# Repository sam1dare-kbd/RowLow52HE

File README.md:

# RowLow52HE

RowLow52HE is a 50% Hall-effect keyboard based on the [HE60](https://github.com/peppapighs/HE60) project. <br>

RowLow52HEは、HE60プロジェクトをベースにして設計した50%の磁気キーボードです。<br>
<br>

---

# Build Guide  

https://note.com/sam1dare/n/naa1372ecf801 <br>
(Japanese text only.)

---

# Important Notes 

This keyboard uses magnetic sensors and may become warm around the MCU during operation. <br>
If you notice abnormal heat generation or unexpected behavior, stop using the device and inspect it before further use.<br><br>

本キーボードは磁気センサーを使用しているため、使用環境によってはMCU周辺が温かくなる場合があります。<br>
異常な発熱や動作不良が発生した場合は、使用を中止してください。

---

# HE60 (Original Project)

Below is the original README from the HE60 project, which this keyboard is based on.

---

# HE60

HE60 is a 60% Hall-effect keyboard PCB with 8kHz polling rate, a split spacebar and Tsangan layout support.

## Features

- Support for GH60 tray mount cases e.g., KBDfans Tofu60 Redux, and KBDfans Holy60.
- Support for gummy O-ring mount cases **if the USB-C port is not soldered** e.g., Bakeneko60, and SingaKBD Unikorn (required 10mm JST cable).
- [libhmk](https://github.com/peppapighs/libhmk) firmware.
- [hmkconf](https://hmk.prasertsuk.com) web-based configurator.

## Disclaimer

- The PCB requires standoffs to be mounted to the switch plate. The mounting points are **not compatible** with other available plates e.g., GEON Venom60 7U plate. HE60 v1 plate **is not compatible** with this PCB.

## Supported Layouts

## Fabrication

The following files are required:

- BOM (Bill of Materials): Contains the list of components required to build the PCB.
- Pick and Place: Contains the placement of the components on the PCB.
- Gerber: Contains the PCB design files for fabrication.

Note that the components in the BOM are all mounted on the bottom side of the PCB, and are based on the available components in JLCPCB at the time of writing. You may need to adjust the components based on your preference or availability. For the JST connector (labeled `JST_SH`), I used `WAFER-SH1.0-4PWB` offered by JLCPCB. **Make sure to deselect the USB-C port when choosing the components to solder if you are using the gummy O-ring version.**

You may change the Hall-effect sensors during the component selection based on your preference, and availability. Different sensors require different calibration values, which can be adjusted using the web-based configurator. Here are some options that I have used:

- GH39FKSW (Cheapest)
- MT9102ET
- SS39ET
- DRV5055A3
- OH49E-S (Discontinued)

The fabrication files above are available [here](https://github.com/peppapighs/HE60/releases).

## Build Guide

The following items are required to build the PCB:

- PCB
- Switch plate (DXF file available [here](/plate.dxf). You may need to use less flexible materials such as aluminum or FR4 to prevent the switch at the top right corner from popping out if you use the alternative backspace layout. If you would like to manufacture FR4 plate along with the PCB, you can find the GERBER file for the plate [here](https://github.com/peppapighs/HE60/releases).)
- Magnetic switches (e.g., GEON Raw HE, Gateron Magnetic Jade, Duhuk Core HE, etc.)
- Stabilizers (**Clip-in stabilizers are required for the gummy O-ring version**)
- M2 3.5mm standoffs x8
- M2 3mm flat head screws x16

1. Install the stabilizers to the PCB.

2. Attach the standoffs to the PCB using the M2 screws.

3. Install the switches to the plate. Assemble the plate and PCB together. Press the PCB against the plate to make sure the switches are seated properly. Screw the standoffs to the plate using the rest of the M2 screws.

4. Install the PCB into the case.

## Firmware

Head to [libhmk](https://github.com/peppapighs/libhmk/releases) for a pre-compiled firmware. The firmware can be flashed using DFU mode, which can be entered by holding the BOOT button before plugging in. You may need to install the DFU bootloader driver using Zadig. See [libhmk](https://github.com/peppapighs/libhmk) for more information for firmware flashing instructions.

## Acknowledgements

- Xelus from AEBoards for reviewing the PCB design and providing feedback.
- Keyboard Atelier community for supporting the project.

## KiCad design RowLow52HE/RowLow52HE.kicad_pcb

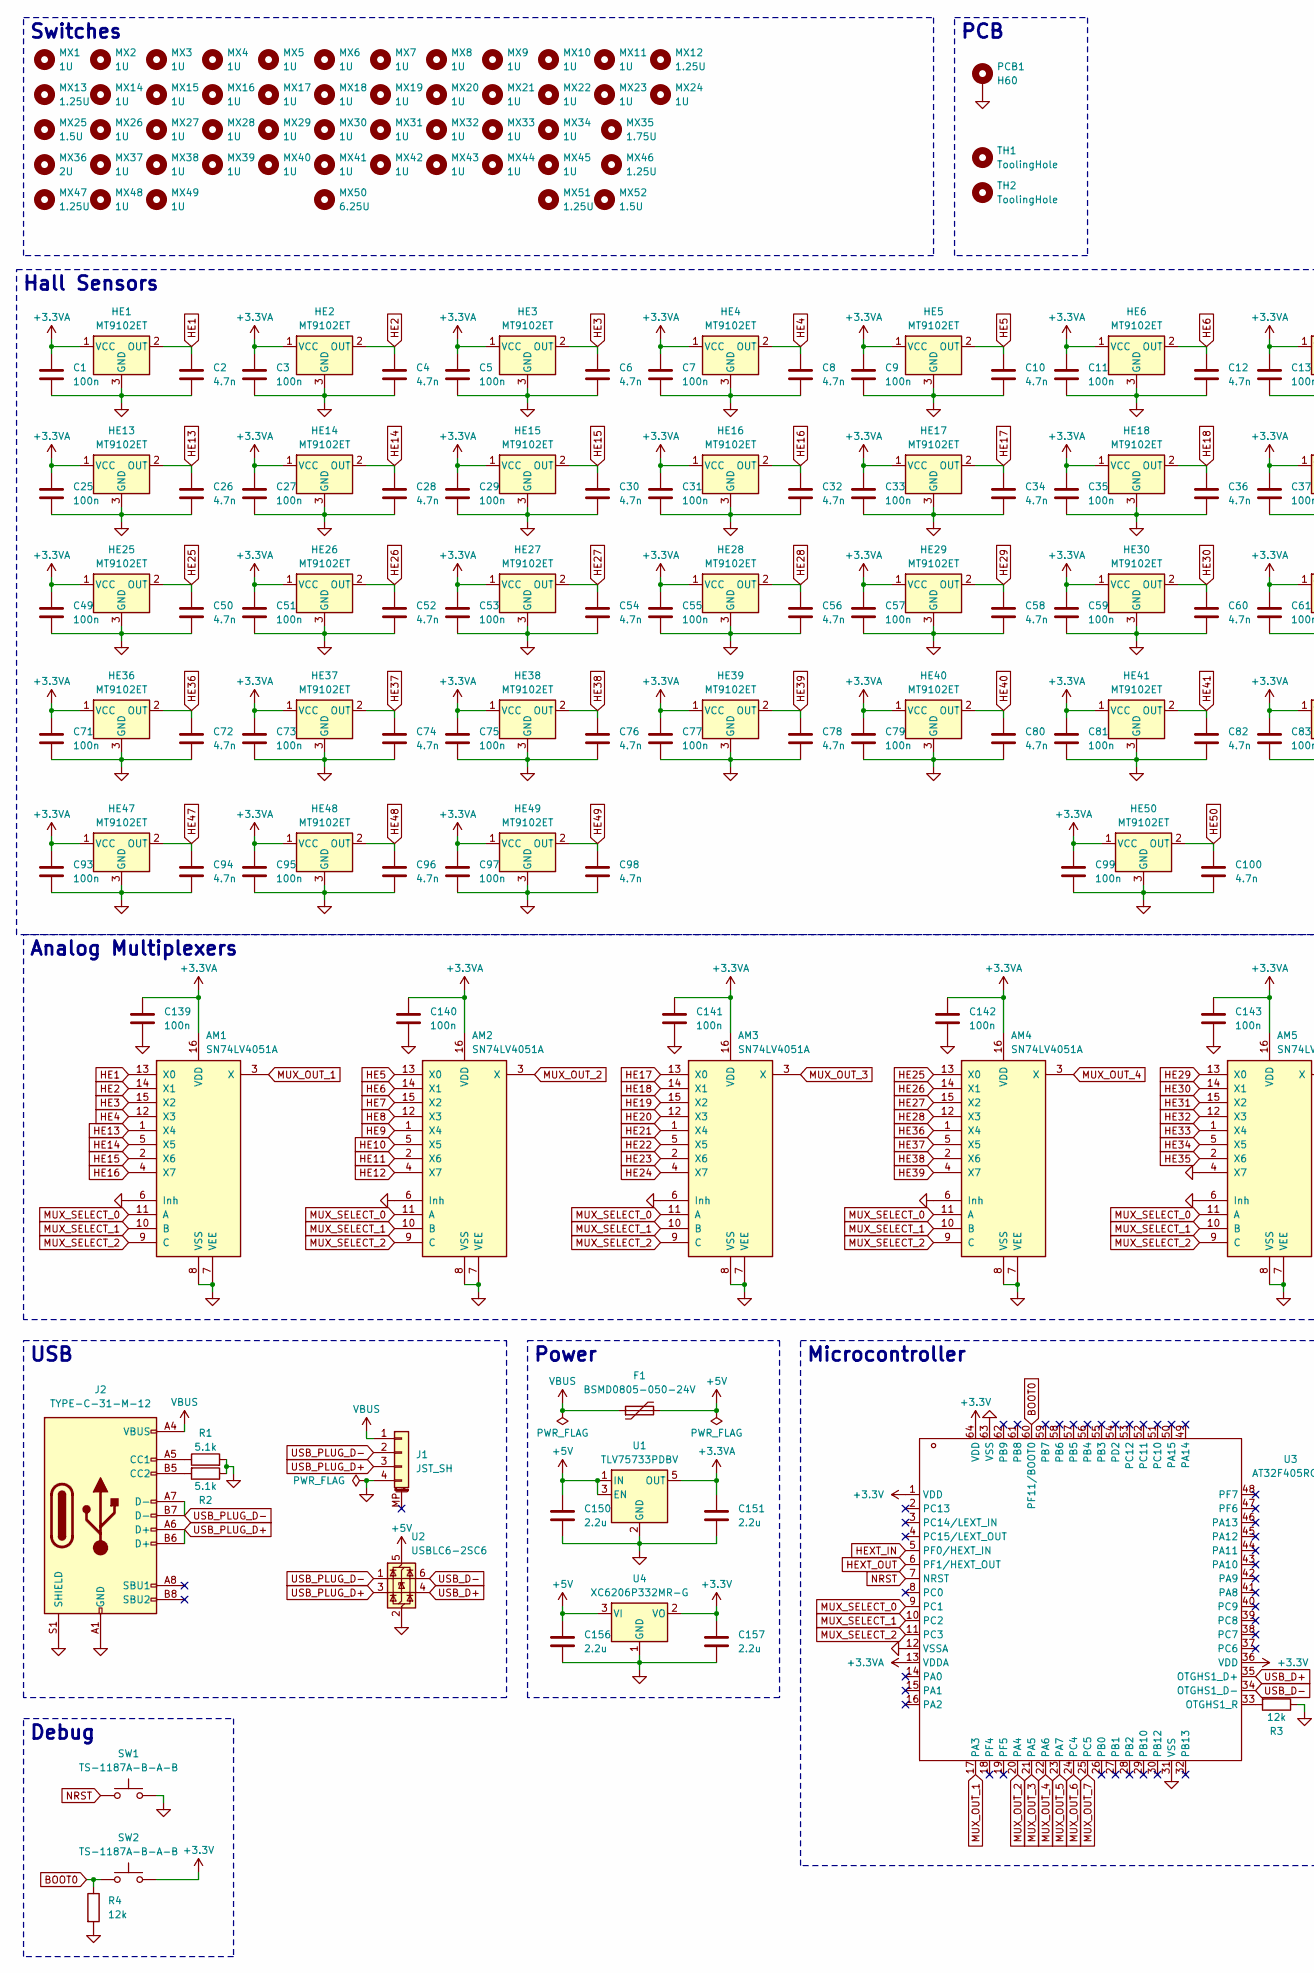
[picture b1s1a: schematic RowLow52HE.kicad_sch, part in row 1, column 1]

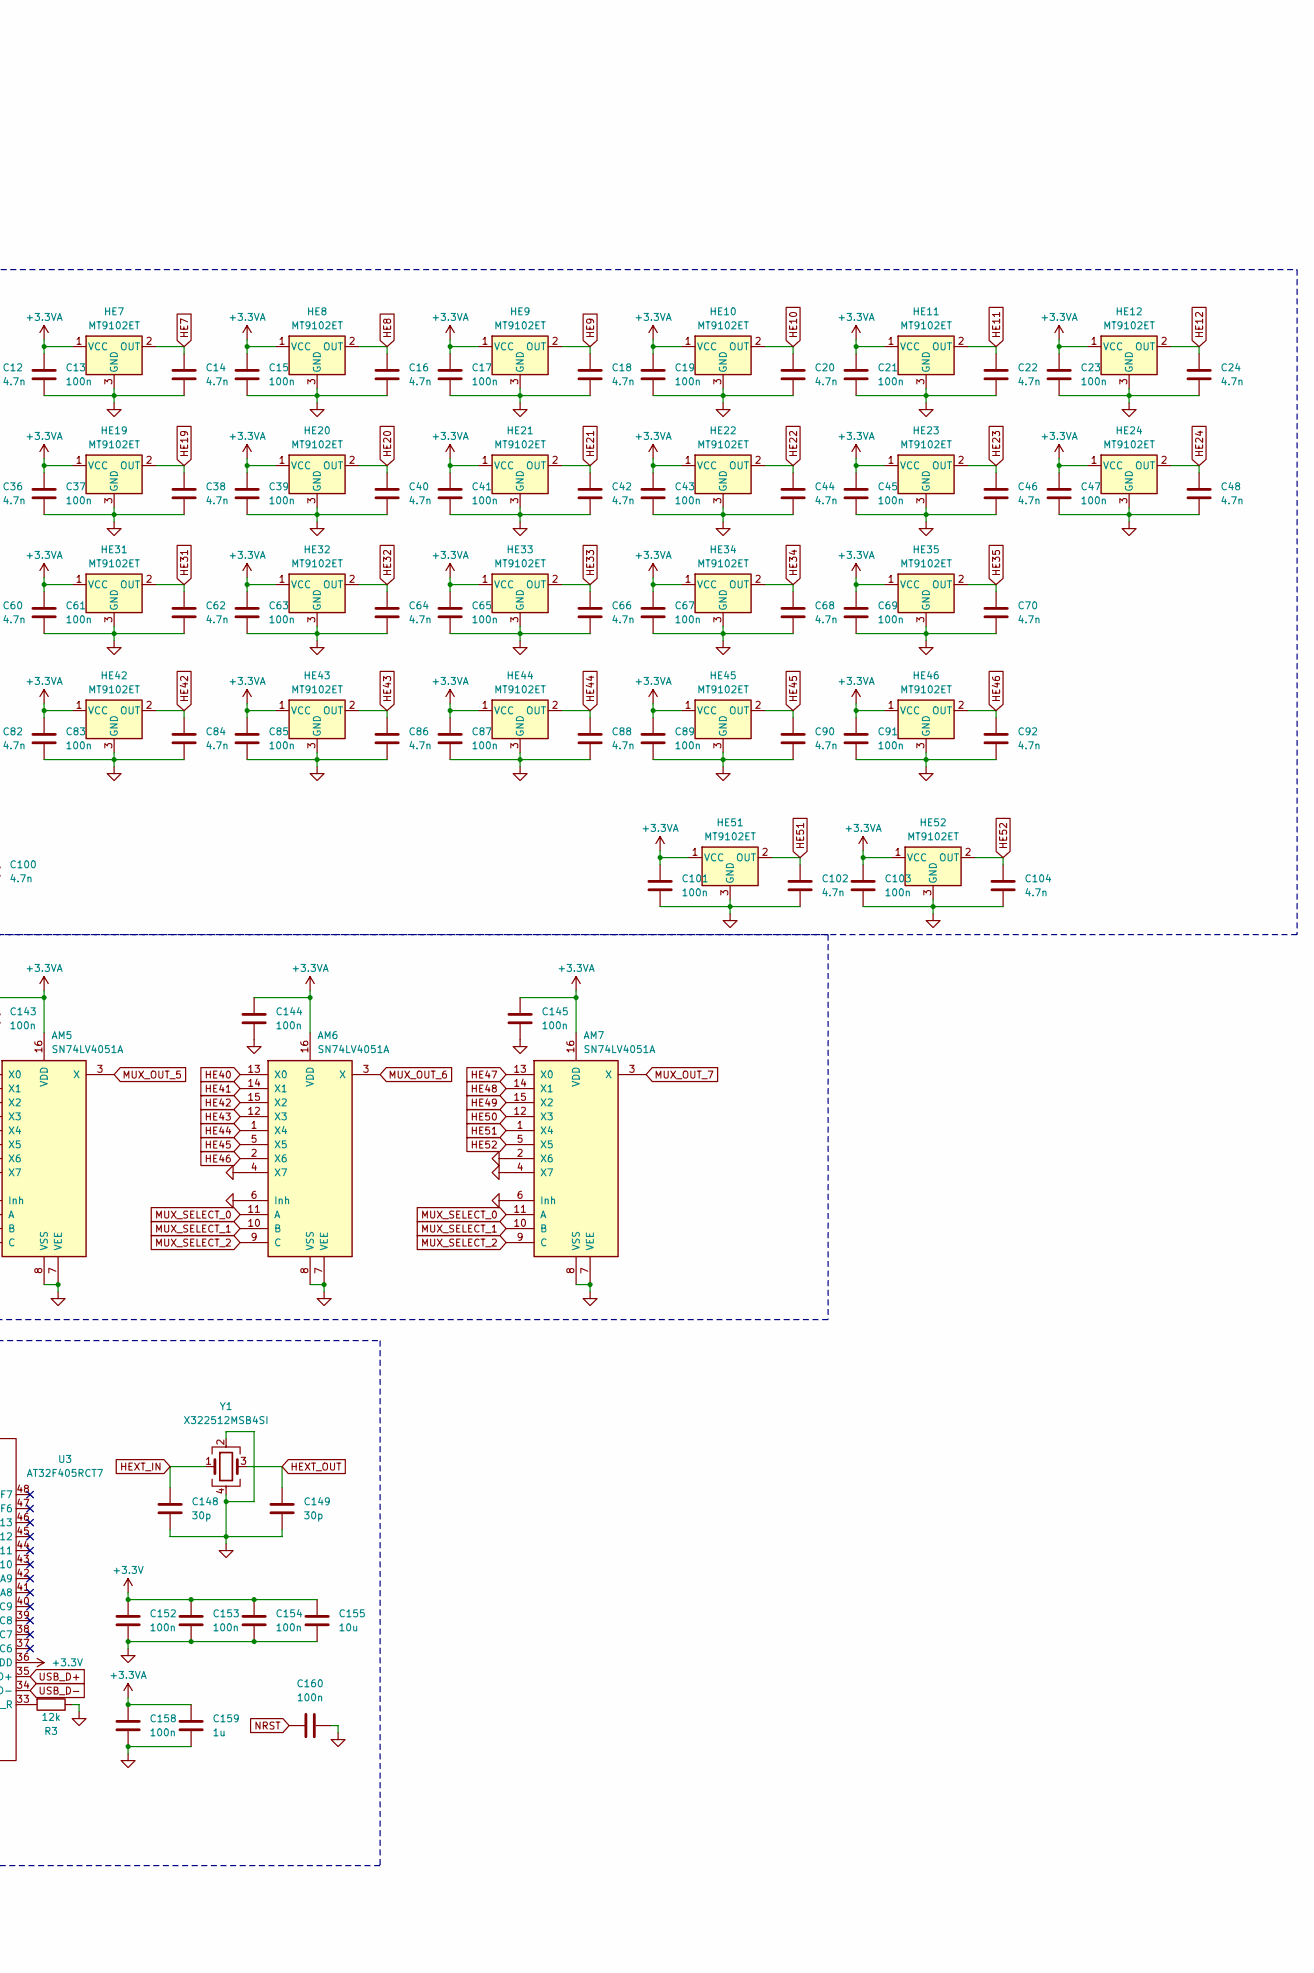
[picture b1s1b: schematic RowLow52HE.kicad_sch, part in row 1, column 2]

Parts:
AM1, AM2, AM3, AM4, AM5, AM6, AM7: SN74LV4051A; TSSOP-16_4.4x5mm_P0.65mm
C1, C3, C5, C7, C9, C11, C13, C15, C17, C19, C21, C23, C25, C27, C29, C31, C33, C35, C37, C39, C41, C43, C45, C47, C49, C51, C53, C55, C57, C59, C61, C63, C65, C67, C69, C71, C73, C75, C77, C79, C81, C83, C85, C87, C89, C91, C93, C95, C97, C99, C101, C103, C139, C140, C141, C142, C143, C144, C145, C152, C153, C154, C158, C160: 100n; C_0402_1005Metric
C2, C4, C6, C8, C10, C12, C14, C16, C18, C20, C22, C24, C26, C28, C30, C32, C34, C36, C38, C40, C42, C44, C46, C48, C50, C52, C54, C56, C58, C60, C62, C64, C66, C68, C70, C72, C74, C76, C78, C80, C82, C84, C86, C88, C90, C92, C94, C96, C98, C100, C102, C104: 4.7n; C_0402_1005Metric
C148, C149: 30p; C_0603_1608Metric
C150, C151, C156, C157: 2.2u; C_0603_1608Metric
C155: 10u; C_0603_1608Metric
C159: 1u; C_0603_1608Metric
F1: BSMD0805-050-24V; Fuse_0805_2012Metric
HE1, HE2, HE3, HE4, HE5, HE6, HE7, HE8, HE9, HE10, HE11, HE12, HE13, HE14, HE15, HE16, HE17, HE18, HE19, HE20, HE21, HE22, HE23, HE24, HE25, HE26, HE27, HE28, HE29, HE30, HE31, HE32, HE33, HE34, HE35, HE36, HE37, HE38, HE39, HE40, HE41, HE42, HE43, HE44, HE45, HE46, HE47, HE48, HE49, HE50, HE51, HE52: MT9102ET; SOT-23-3
J1: JST_SH; JST_SH_SM04B-SRSS-TB_1x04-1MP_P1.00mm_Horizontal
J2: TYPE-C-31-M-12; USB_C_Receptacle_HRO_TYPE-C-31-M-12
MX1, MX2, MX3, MX4, MX5, MX6, MX7, MX8, MX9, MX10, MX11, MX14, MX15, MX16, MX17, MX18, MX19, MX20, MX21, MX22, MX23, MX24, MX26, MX27, MX28, MX29, MX30, MX31, MX32, MX33, MX34, MX37, MX38, MX39, MX40, MX41, MX42, MX43, MX44, MX45, MX48, MX49: 1U; MX-1U
MX12, MX13, MX46, MX47, MX51: 1.25U; MX-1.25U
MX25, MX52: 1.5U; MX-1.5U
MX35: 1.75U; MX-1.75U
MX36: 2U; MX-2U
MX50: 6.25U; MX-6.25U-ReversedStabilizers
PCB1: H60
R1, R2: 5.1k; R_0402_1005Metric
R3, R4: 12k; R_0402_1005Metric
SW1, SW2: TS-1187A-B-A-B; SW_Push_1P1T_XKB_TS-1187A
TH1, TH2: ToolingHole
U1: TLV75733PDBV; SOT-23-5
U2: USBLC6-2SC6; SOT-23-6
U3: AT32F405RCT7; LQFP-64_10x10mm_P0.5mm
U4: XC6206P332MR-G; SOT-23-3
Y1: X322512MSB4SI; Crystal_SMD_3225-4Pin_3.2x2.5mm

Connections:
+3.3V: C152.1, C153.1, C154.1, C155.1, C157.1, SW2.2, U3.1 (VDD), U3.36 (VDD), U3.64 (VDD), U4.2 (VO)
+3.3VA: AM1.16 (VDD), AM2.16 (VDD), AM3.16 (VDD), AM4.16 (VDD), AM5.16 (VDD), AM6.16 (VDD), AM7.16 (VDD), C1.1, C3.1, C5.1, C7.1, C9.1, C11.1, C13.1, C15.1, C17.1, C19.1, C21.1, C23.1, C25.1, C27.1, C29.1, C31.1, C33.1, C35.1, C37.1, C39.1, C41.1, C43.1, C45.1, C47.1, C49.1, C51.1, C53.1, C55.1, C57.1, C59.1, C61.1, C63.1, C65.1, C67.1, C69.1, C71.1, C73.1, C75.1, C77.1, C79.1, C81.1, C83.1, C85.1, C87.1, C89.1, C91.1, C93.1, C95.1, C97.1, C99.1, C101.1, C103.1, C139.1, C140.1, C141.1, C142.1, C143.1, C144.1, C145.1, C151.1, C158.1, C159.1, HE1.1 (VCC), HE2.1 (VCC), HE3.1 (VCC), HE4.1 (VCC), HE5.1 (VCC), HE6.1 (VCC), HE7.1 (VCC), HE8.1 (VCC), HE9.1 (VCC), HE10.1 (VCC), HE11.1 (VCC), HE12.1 (VCC), HE13.1 (VCC), HE14.1 (VCC), HE15.1 (VCC), HE16.1 (VCC), HE17.1 (VCC), HE18.1 (VCC), HE19.1 (VCC), HE20.1 (VCC), HE21.1 (VCC), HE22.1 (VCC), HE23.1 (VCC), HE24.1 (VCC), HE25.1 (VCC), HE26.1 (VCC), HE27.1 (VCC), HE28.1 (VCC), HE29.1 (VCC), HE30.1 (VCC), HE31.1 (VCC), HE32.1 (VCC), HE33.1 (VCC), HE34.1 (VCC), HE35.1 (VCC), HE36.1 (VCC), HE37.1 (VCC), HE38.1 (VCC), HE39.1 (VCC), HE40.1 (VCC), HE41.1 (VCC), HE42.1 (VCC), HE43.1 (VCC), HE44.1 (VCC), HE45.1 (VCC), HE46.1 (VCC), HE47.1 (VCC), HE48.1 (VCC), HE49.1 (VCC), HE50.1 (VCC), HE51.1 (VCC), HE52.1 (VCC), U1.5 (OUT), U3.13 (VDDA)
+5V: C150.1, C156.1, F1.2, U1.1 (IN), U1.3 (EN), U2.5 (VBUS), U4.3 (VI)
BOOT0: R4.1, SW2.1, U3.60 (PF11/BOOT0)
GND: AM1.6 (Inh), AM1.7 (VEE), AM1.8 (VSS), AM2.6 (Inh), AM2.7 (VEE), AM2.8 (VSS), AM3.6 (Inh), AM3.7 (VEE), AM3.8 (VSS), AM4.6 (Inh), AM4.7 (VEE), AM4.8 (VSS), AM5.4 (X7), AM5.6 (Inh), AM5.7 (VEE), AM5.8 (VSS), AM6.4 (X7), AM6.6 (Inh), AM6.7 (VEE), AM6.8 (VSS), AM7.2 (X6), AM7.4 (X7), AM7.6 (Inh), AM7.7 (VEE), AM7.8 (VSS), C1.2, C2.2, C3.2, C4.2, C5.2, C6.2, C7.2, C8.2, C9.2, C10.2, C11.2, C12.2, C13.2, C14.2, C15.2, C16.2, C17.2, C18.2, C19.2, C20.2, C21.2, C22.2, C23.2, C24.2, C25.2, C26.2, C27.2, C28.2, C29.2, C30.2, C31.2, C32.2, C33.2, C34.2, C35.2, C36.2, C37.2, C38.2, C39.2, C40.2, C41.2, C42.2, C43.2, C44.2, C45.2, C46.2, C47.2, C48.2, C49.2, C50.2, C51.2, C52.2, C53.2, C54.2, C55.2, C56.2, C57.2, C58.2, C59.2, C60.2, C61.2, C62.2, C63.2, C64.2, C65.2, C66.2, C67.2, C68.2, C69.2, C70.2, C71.2, C72.2, C73.2, C74.2, C75.2, C76.2, C77.2, C78.2, C79.2, C80.2, C81.2, C82.2, C83.2, C84.2, C85.2, C86.2, C87.2, C88.2, C89.2, C90.2, C91.2, C92.2, C93.2, C94.2, C95.2, C96.2, C97.2, C98.2, C99.2, C100.2, C101.2, C102.2, C103.2, C104.2, C139.2, C140.2, C141.2, C142.2, C143.2, C144.2, C145.2, C148.2, C149.2, C150.2, C151.2, C152.2, C153.2, C154.2, C155.2, C156.2, C157.2, C158.2, C159.2, C160.2, HE1.3 (GND), HE2.3 (GND), HE3.3 (GND), HE4.3 (GND), HE5.3 (GND), HE6.3 (GND), HE7.3 (GND), HE8.3 (GND), HE9.3 (GND), HE10.3 (GND), HE11.3 (GND), HE12.3 (GND), HE13.3 (GND), HE14.3 (GND), HE15.3 (GND), HE16.3 (GND), HE17.3 (GND), HE18.3 (GND), HE19.3 (GND), HE20.3 (GND), HE21.3 (GND), HE22.3 (GND), HE23.3 (GND), HE24.3 (GND), HE25.3 (GND), HE26.3 (GND), HE27.3 (GND), HE28.3 (GND), HE29.3 (GND), HE30.3 (GND), HE31.3 (GND), HE32.3 (GND), HE33.3 (GND), HE34.3 (GND), HE35.3 (GND), HE36.3 (GND), HE37.3 (GND), HE38.3 (GND), HE39.3 (GND), HE40.3 (GND), HE41.3 (GND), HE42.3 (GND), HE43.3 (GND), HE44.3 (GND), HE45.3 (GND), HE46.3 (GND), HE47.3 (GND), HE48.3 (GND), HE49.3 (GND), HE50.3 (GND), HE51.3 (GND), HE52.3 (GND), J1.4, J2.A1 (GND), J2.A12 (GND), J2.B1 (GND), J2.B12 (GND), J2.S1 (SHIELD), PCB1.1, R1.2, R2.1, R3.1, R4.2, SW1.2, U1.2 (GND), U2.2 (GND), U3.12 (VSSA), U3.31 (VSS), U3.63 (VSS), U4.1 (GND), Y1.2, Y1.4
HE1: AM1.13 (X0), C2.1, HE1.2 (OUT)
HE2: AM1.14 (X1), C4.1, HE2.2 (OUT)
HE3: AM1.15 (X2), C6.1, HE3.2 (OUT)
HE4: AM1.12 (X3), C8.1, HE4.2 (OUT)
HE5: AM2.13 (X0), C10.1, HE5.2 (OUT)
HE6: AM2.14 (X1), C12.1, HE6.2 (OUT)
HE7: AM2.15 (X2), C14.1, HE7.2 (OUT)
HE8: AM2.12 (X3), C16.1, HE8.2 (OUT)
HE9: AM2.1 (X4), C18.1, HE9.2 (OUT)
HE10: AM2.5 (X5), C20.1, HE10.2 (OUT)
HE11: AM2.2 (X6), C22.1, HE11.2 (OUT)
HE12: AM2.4 (X7), C24.1, HE12.2 (OUT)
HE13: AM1.1 (X4), C26.1, HE13.2 (OUT)
HE14: AM1.5 (X5), C28.1, HE14.2 (OUT)
HE15: AM1.2 (X6), C30.1, HE15.2 (OUT)
HE16: AM1.4 (X7), C32.1, HE16.2 (OUT)
HE17: AM3.13 (X0), C34.1, HE17.2 (OUT)
HE18: AM3.14 (X1), C36.1, HE18.2 (OUT)
HE19: AM3.15 (X2), C38.1, HE19.2 (OUT)
HE20: AM3.12 (X3), C40.1, HE20.2 (OUT)
HE21: AM3.1 (X4), C42.1, HE21.2 (OUT)
HE22: AM3.5 (X5), C44.1, HE22.2 (OUT)
HE23: AM3.2 (X6), C46.1, HE23.2 (OUT)
HE24: AM3.4 (X7), C48.1, HE24.2 (OUT)
HE25: AM4.13 (X0), C50.1, HE25.2 (OUT)
HE26: AM4.14 (X1), C52.1, HE26.2 (OUT)
HE27: AM4.15 (X2), C54.1, HE27.2 (OUT)
HE28: AM4.12 (X3), C56.1, HE28.2 (OUT)
HE29: AM5.13 (X0), C58.1, HE29.2 (OUT)
HE30: AM5.14 (X1), C60.1, HE30.2 (OUT)
HE31: AM5.15 (X2), C62.1, HE31.2 (OUT)
HE32: AM5.12 (X3), C64.1, HE32.2 (OUT)
HE33: AM5.1 (X4), C66.1, HE33.2 (OUT)
HE34: AM5.5 (X5), C68.1, HE34.2 (OUT)
HE35: AM5.2 (X6), C70.1, HE35.2 (OUT)
HE36: AM4.1 (X4), C72.1, HE36.2 (OUT)
HE37: AM4.5 (X5), C74.1, HE37.2 (OUT)
HE38: AM4.2 (X6), C76.1, HE38.2 (OUT)
HE39: AM4.4 (X7), C78.1, HE39.2 (OUT)
HE40: AM6.13 (X0), C80.1, HE40.2 (OUT)
HE41: AM6.14 (X1), C82.1, HE41.2 (OUT)
HE42: AM6.15 (X2), C84.1, HE42.2 (OUT)
HE43: AM6.12 (X3), C86.1, HE43.2 (OUT)
HE44: AM6.1 (X4), C88.1, HE44.2 (OUT)
HE45: AM6.5 (X5), C90.1, HE45.2 (OUT)
HE46: AM6.2 (X6), C92.1, HE46.2 (OUT)
HE47: AM7.13 (X0), C94.1, HE47.2 (OUT)
HE48: AM7.14 (X1), C96.1, HE48.2 (OUT)
HE49: AM7.15 (X2), C98.1, HE49.2 (OUT)
HE50: AM7.12 (X3), C100.1, HE50.2 (OUT)
HE51: AM7.1 (X4), C102.1, HE51.2 (OUT)
HE52: AM7.5 (X5), C104.1, HE52.2 (OUT)
HEXT_IN: C148.1, U3.5 (PF0/HEXT_IN), Y1.1
HEXT_OUT: C149.1, U3.6 (PF1/HEXT_OUT), Y1.3
MUX_OUT_1: AM1.3 (X), U3.17 (PA3)
MUX_OUT_2: AM2.3 (X), U3.20 (PA4)
MUX_OUT_3: AM3.3 (X), U3.21 (PA5)
MUX_OUT_4: AM4.3 (X), U3.22 (PA6)
MUX_OUT_5: AM5.3 (X), U3.23 (PA7)
MUX_OUT_6: AM6.3 (X), U3.24 (PC4)
MUX_OUT_7: AM7.3 (X), U3.25 (PC5)
MUX_SELECT_0: AM1.11 (A), AM2.11 (A), AM3.11 (A), AM4.11 (A), AM5.11 (A), AM6.11 (A), AM7.11 (A), U3.9 (PC1)
MUX_SELECT_1: AM1.10 (B), AM2.10 (B), AM3.10 (B), AM4.10 (B), AM5.10 (B), AM6.10 (B), AM7.10 (B), U3.10 (PC2)
MUX_SELECT_2: AM1.9 (C), AM2.9 (C), AM3.9 (C), AM4.9 (C), AM5.9 (C), AM6.9 (C), AM7.9 (C), U3.11 (PC3)
NRST: C160.1, SW1.1, U3.7 (NRST)
unnamed: J2.A5 (CC1), R1.1
unnamed: J2.B5 (CC2), R2.2
unnamed: R3.2, U3.33 (OTGHS1_R)
USB_D+: U2.4 (I/O2), U3.35 (OTGHS1_D+)
USB_D-: U2.6 (I/O1), U3.34 (OTGHS1_D-)
USB_PLUG_D+: J1.3, J2.A6 (D+), J2.B6 (D+), U2.3 (I/O2)
USB_PLUG_D-: J1.2, J2.A7 (D-), J2.B7 (D-), U2.1 (I/O1)
VBUS: F1.1, J1.1, J2.A4 (VBUS), J2.A9 (VBUS), J2.B4 (VBUS), J2.B9 (VBUS)

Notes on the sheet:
PCB
Hall Sensors
Switches
USB
Analog Multiplexers
Power
Debug
Microcontroller

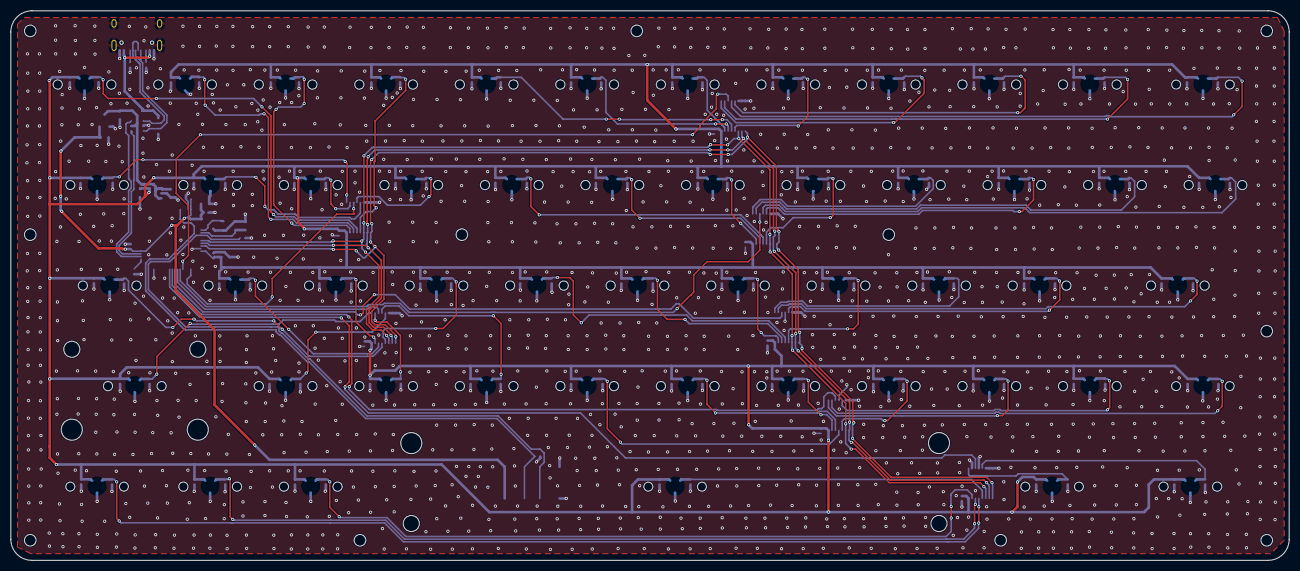
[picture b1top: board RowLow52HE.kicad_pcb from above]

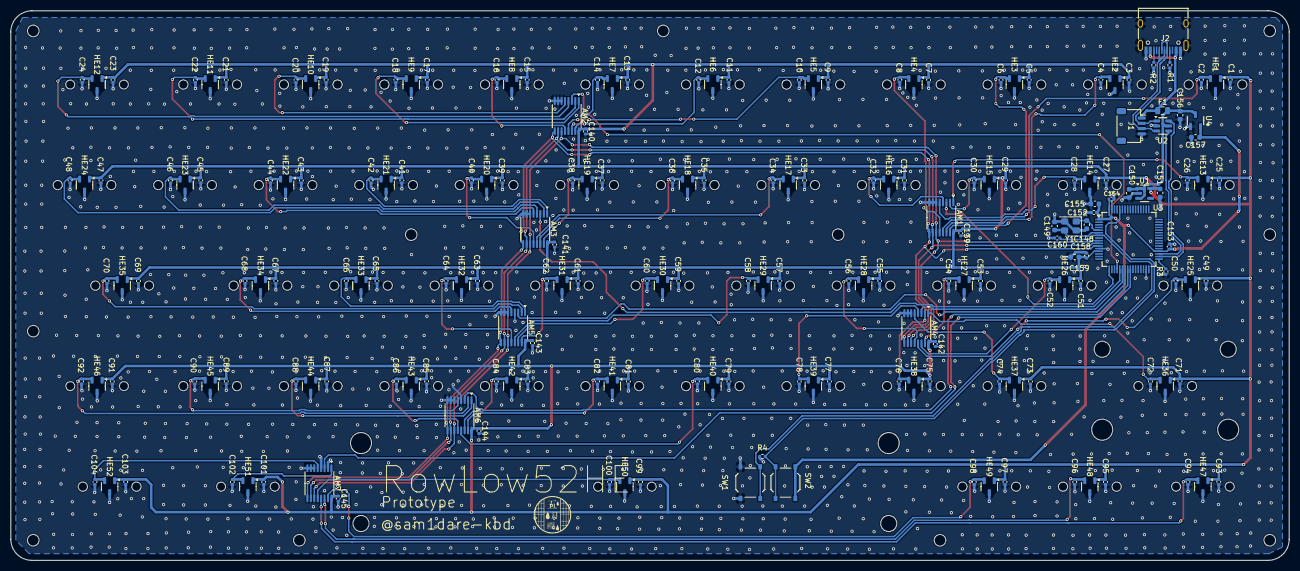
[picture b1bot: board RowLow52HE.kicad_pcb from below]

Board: 2 copper layers, 242.2 x 104.1 mm, 260 parts (197 on the bottom side), 78 nets.

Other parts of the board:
Ref**: Val**; m2_Screw_Hole
Ref**#2, Ref**#3, Ref**#4, Ref**#5, Ref**#6, Ref**#7, Ref**#8, Ref**#9, Ref**#10, Ref**#11: Val**; m2_Screw_Hole
